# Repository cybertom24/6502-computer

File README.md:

# 6502-computer
My personal repo to build a breadboard version of a computer around the 6502 uProcessor. This project is inspired by the 6502 computer made by Ben Eater (https://eater.net/6502)

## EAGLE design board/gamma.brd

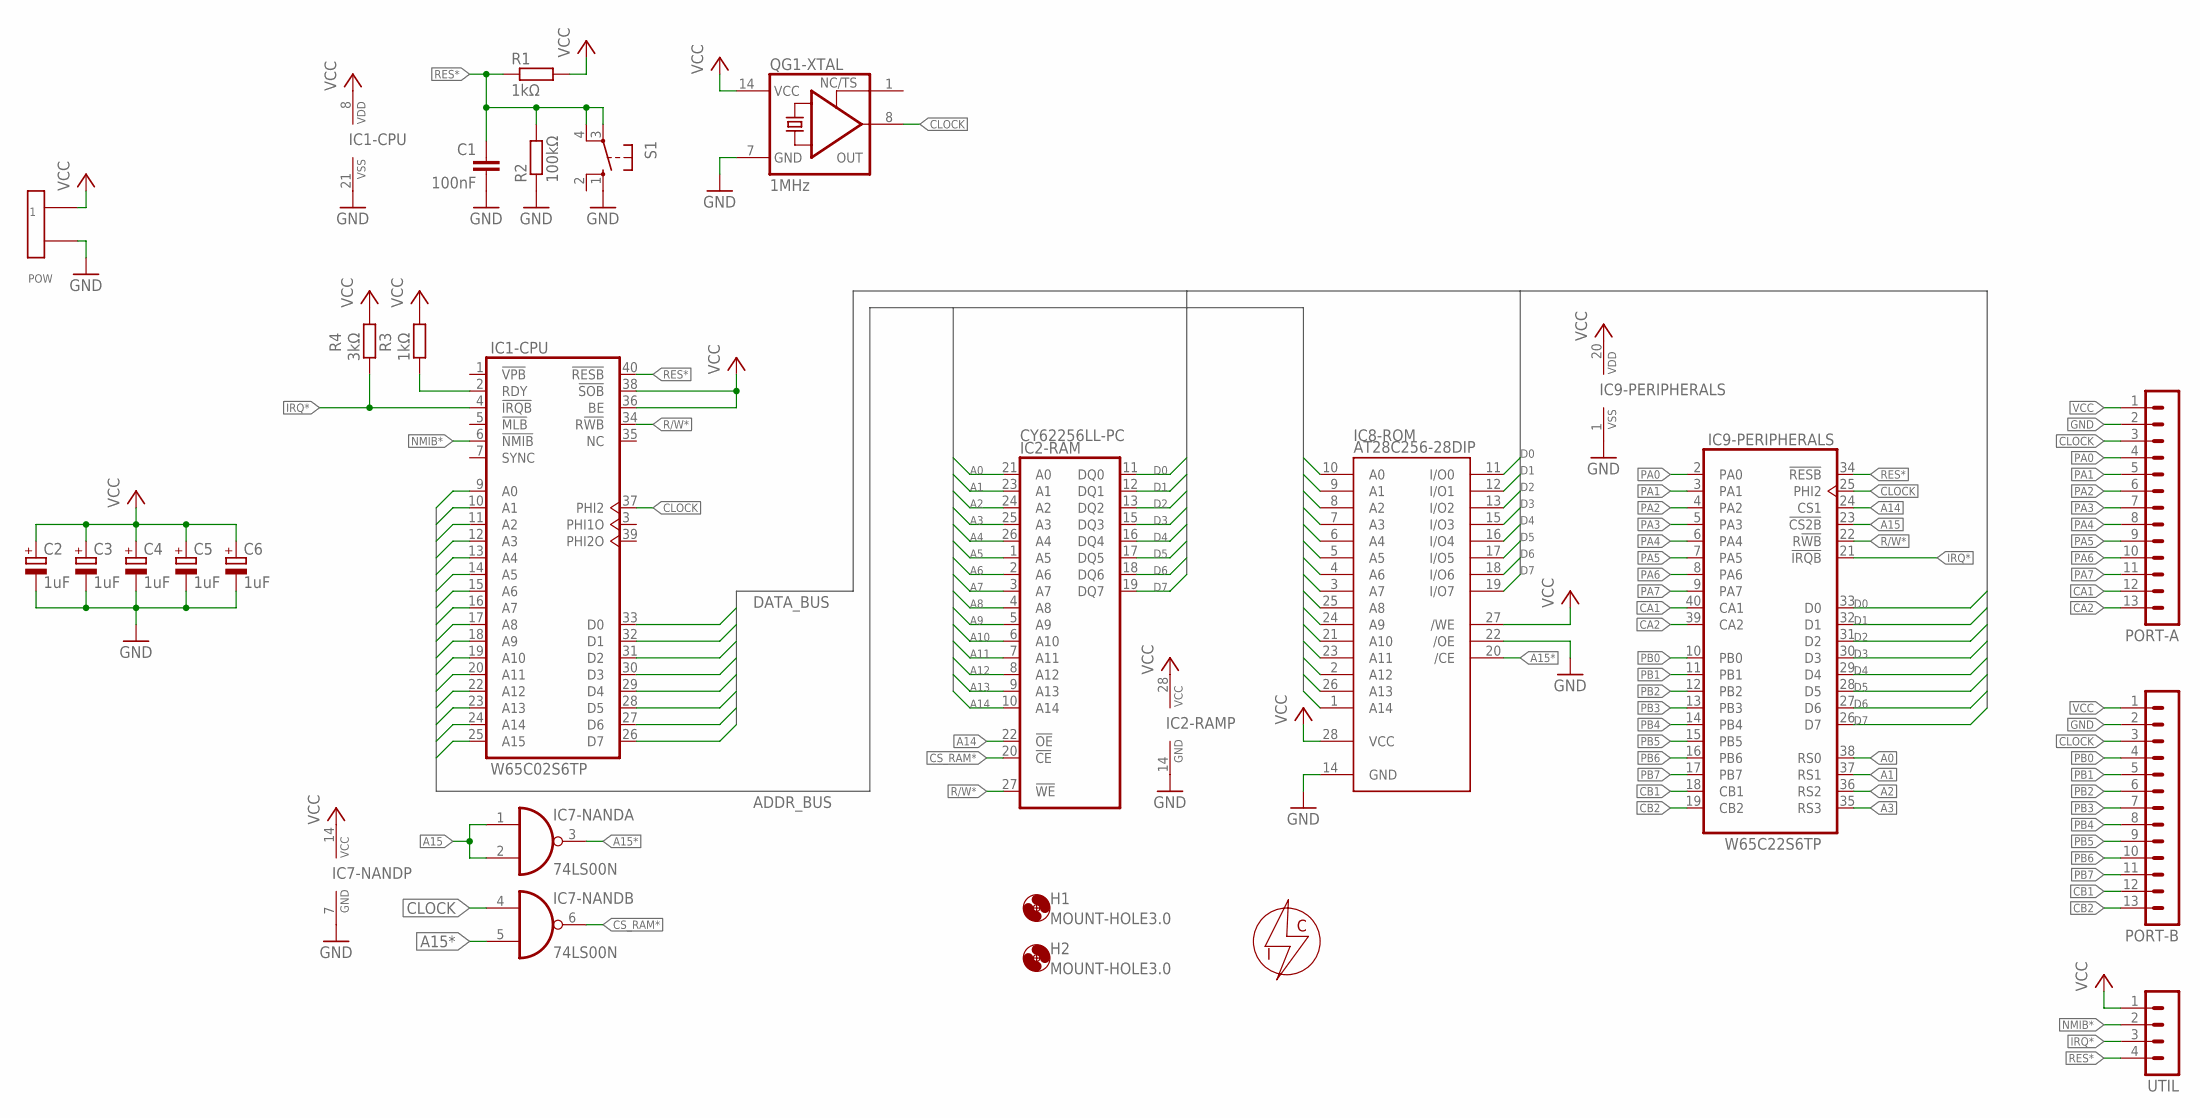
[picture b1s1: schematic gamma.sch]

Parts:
C1: 100nF; C050-025X075
C2, C3, C4, C5, C6: 1uF; E2-5
H1, H2: MOUNT-HOLE3.0; 3,0
IC1-CPU: W65C02S6TP; DIL40
IC2-RAM: CY62256LL-PC; DIL28-6
IC7-NAND: 74LS00N; DIL14
IC8-ROM: AT28C256-28DIP; DIL28-6
IC9-PERIPHERALS: W65C22S6TP; DIL40
PORT-A: MA13-1
PORT-B: MA13-1
POW: AK500; AK500-2
QG1-XTAL: 1MHz; DIL14S
R1, R3: 1kΩ; 0207/10
R2: 100kΩ; 0207/10
R4: 3kΩ; 0207/10
S1: 10-XX; B3F-10XX
U$1: LOGO-CYBERINDUSTRIES"; LOGO-SMALL
UTIL: MA04-1

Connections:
A0: IC1-CPU.9 (A0), IC2-RAM.21 (A0), IC8-ROM.10 (A0), IC9-PERIPHERALS.38 (RS0)
A1: IC1-CPU.10 (A1), IC2-RAM.23 (A1), IC8-ROM.9 (A1), IC9-PERIPHERALS.37 (RS1)
A2: IC1-CPU.11 (A2), IC2-RAM.24 (A2), IC8-ROM.8 (A2), IC9-PERIPHERALS.36 (RS2)
A3: IC1-CPU.12 (A3), IC2-RAM.25 (A3), IC8-ROM.7 (A3), IC9-PERIPHERALS.35 (RS3)
A4: IC1-CPU.13 (A4), IC2-RAM.26 (A4), IC8-ROM.6 (A4)
A5: IC1-CPU.14 (A5), IC2-RAM.1 (A5), IC8-ROM.5 (A5)
A6: IC1-CPU.15 (A6), IC2-RAM.2 (A6), IC8-ROM.4 (A6)
A7: IC1-CPU.16 (A7), IC2-RAM.3 (A7), IC8-ROM.3 (A7)
A8: IC1-CPU.17 (A8), IC2-RAM.4 (A8), IC8-ROM.25 (A8)
A9: IC1-CPU.18 (A9), IC2-RAM.5 (A9), IC8-ROM.24 (A9)
A10: IC1-CPU.19 (A10), IC2-RAM.6 (A10), IC8-ROM.21 (A10)
A11: IC1-CPU.20 (A11), IC2-RAM.7 (A11), IC8-ROM.23 (A11)
A12: IC1-CPU.22 (A12), IC2-RAM.8 (A12), IC8-ROM.2 (A12)
A13: IC1-CPU.23 (A13), IC2-RAM.9 (A13), IC8-ROM.26 (A13)
A14: IC1-CPU.24 (A14), IC2-RAM.10 (A14), IC2-RAM.22 (!OE), IC8-ROM.1 (A14), IC9-PERIPHERALS.24 (CS1)
A15: IC1-CPU.25 (A15), IC7-NAND.1 (I0), IC7-NAND.2 (I1), IC9-PERIPHERALS.23 (!CS2B)
A15*: IC7-NAND.3 (O), IC7-NAND.5 (I1), IC8-ROM.20 (/CE)
CA1: IC9-PERIPHERALS.40 (CA1), PORT-A.12
CA2: IC9-PERIPHERALS.39 (CA2), PORT-A.13
CB1: IC9-PERIPHERALS.18 (CB1), PORT-B.12
CB2: IC9-PERIPHERALS.19 (CB2), PORT-B.13
CLOCK: IC1-CPU.37 (PHI2), IC7-NAND.4 (I0), IC9-PERIPHERALS.25 (PHI2), PORT-A.3, PORT-B.3, QG1-XTAL.8 (OUT)
CS_RAM*: IC2-RAM.20 (!CE), IC7-NAND.6 (O)
D0: IC1-CPU.33 (D0), IC2-RAM.11 (DQ0), IC8-ROM.11 (I/O0), IC9-PERIPHERALS.33 (D0)
D1: IC1-CPU.32 (D1), IC2-RAM.12 (DQ1), IC8-ROM.12 (I/O1), IC9-PERIPHERALS.32 (D1)
D2: IC1-CPU.31 (D2), IC2-RAM.13 (DQ2), IC8-ROM.13 (I/O2), IC9-PERIPHERALS.31 (D2)
D3: IC1-CPU.30 (D3), IC2-RAM.15 (DQ3), IC8-ROM.15 (I/O3), IC9-PERIPHERALS.30 (D3)
D4: IC1-CPU.29 (D4), IC2-RAM.16 (DQ4), IC8-ROM.16 (I/O4), IC9-PERIPHERALS.29 (D4)
D5: IC1-CPU.28 (D5), IC2-RAM.17 (DQ5), IC8-ROM.17 (I/O5), IC9-PERIPHERALS.28 (D5)
D6: IC1-CPU.27 (D6), IC2-RAM.18 (DQ6), IC8-ROM.18 (I/O6), IC9-PERIPHERALS.27 (D6)
D7: IC1-CPU.26 (D7), IC2-RAM.19 (DQ7), IC8-ROM.19 (I/O7), IC9-PERIPHERALS.26 (D7)
GND: C1.2, C2.-, C3.-, C4.-, C5.-, C6.-, IC1-CPU.21 (VSS), IC2-RAM.14 (GND), IC7-NAND.7 (GND), IC8-ROM.14 (GND), IC8-ROM.22 (/OE), IC9-PERIPHERALS.1 (VSS), PORT-A.2, PORT-B.2, POW.P$2, QG1-XTAL.7 (GND), R2.1, S1.1 (S)
IRQ*: IC1-CPU.4 (!IRQB), IC9-PERIPHERALS.21 (!IRQB), R4.2, UTIL.3
unnamed: IC1-CPU.2 (RDY), R3.2
NMIB*: IC1-CPU.6 (!NMIB), UTIL.2
PA0: IC9-PERIPHERALS.2 (PA0), PORT-A.4
PA1: IC9-PERIPHERALS.3 (PA1), PORT-A.5
PA2: IC9-PERIPHERALS.4 (PA2), PORT-A.6
PA3: IC9-PERIPHERALS.5 (PA3), PORT-A.7
PA4: IC9-PERIPHERALS.6 (PA4), PORT-A.8
PA5: IC9-PERIPHERALS.7 (PA5), PORT-A.9
PA6: IC9-PERIPHERALS.8 (PA6), PORT-A.10
PA7: IC9-PERIPHERALS.9 (PA7), PORT-A.11
PB0: IC9-PERIPHERALS.10 (PB0), PORT-B.4
PB1: IC9-PERIPHERALS.11 (PB1), PORT-B.5
PB2: IC9-PERIPHERALS.12 (PB2), PORT-B.6
PB3: IC9-PERIPHERALS.13 (PB3), PORT-B.7
PB4: IC9-PERIPHERALS.14 (PB4), PORT-B.8
PB5: IC9-PERIPHERALS.15 (PB5), PORT-B.9
PB6: IC9-PERIPHERALS.16 (PB6), PORT-B.10
PB7: IC9-PERIPHERALS.17 (PB7), PORT-B.11
R/W*: IC1-CPU.34 (R!WB), IC2-RAM.27 (!WE), IC9-PERIPHERALS.22 (R!WB)
RES*: C1.1, IC1-CPU.40 (!RESB), IC9-PERIPHERALS.34 (!RESB), R1.1, R2.2, S1.3, S1.4 (P1), UTIL.4
VCC: C2.+, C3.+, C4.+, C5.+, C6.+, IC1-CPU.8 (VDD), IC1-CPU.36 (BE), IC1-CPU.38 (!SOB), IC2-RAM.28 (VCC), IC7-NAND.14 (VCC), IC8-ROM.27 (/WE), IC8-ROM.28 (VCC), IC9-PERIPHERALS.20 (VDD), PORT-A.1, PORT-B.1, POW.P$1, QG1-XTAL.14 (VCC), R1.2, R3.1, R4.1, UTIL.1

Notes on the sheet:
DATA_BUS
ADDR_BUS

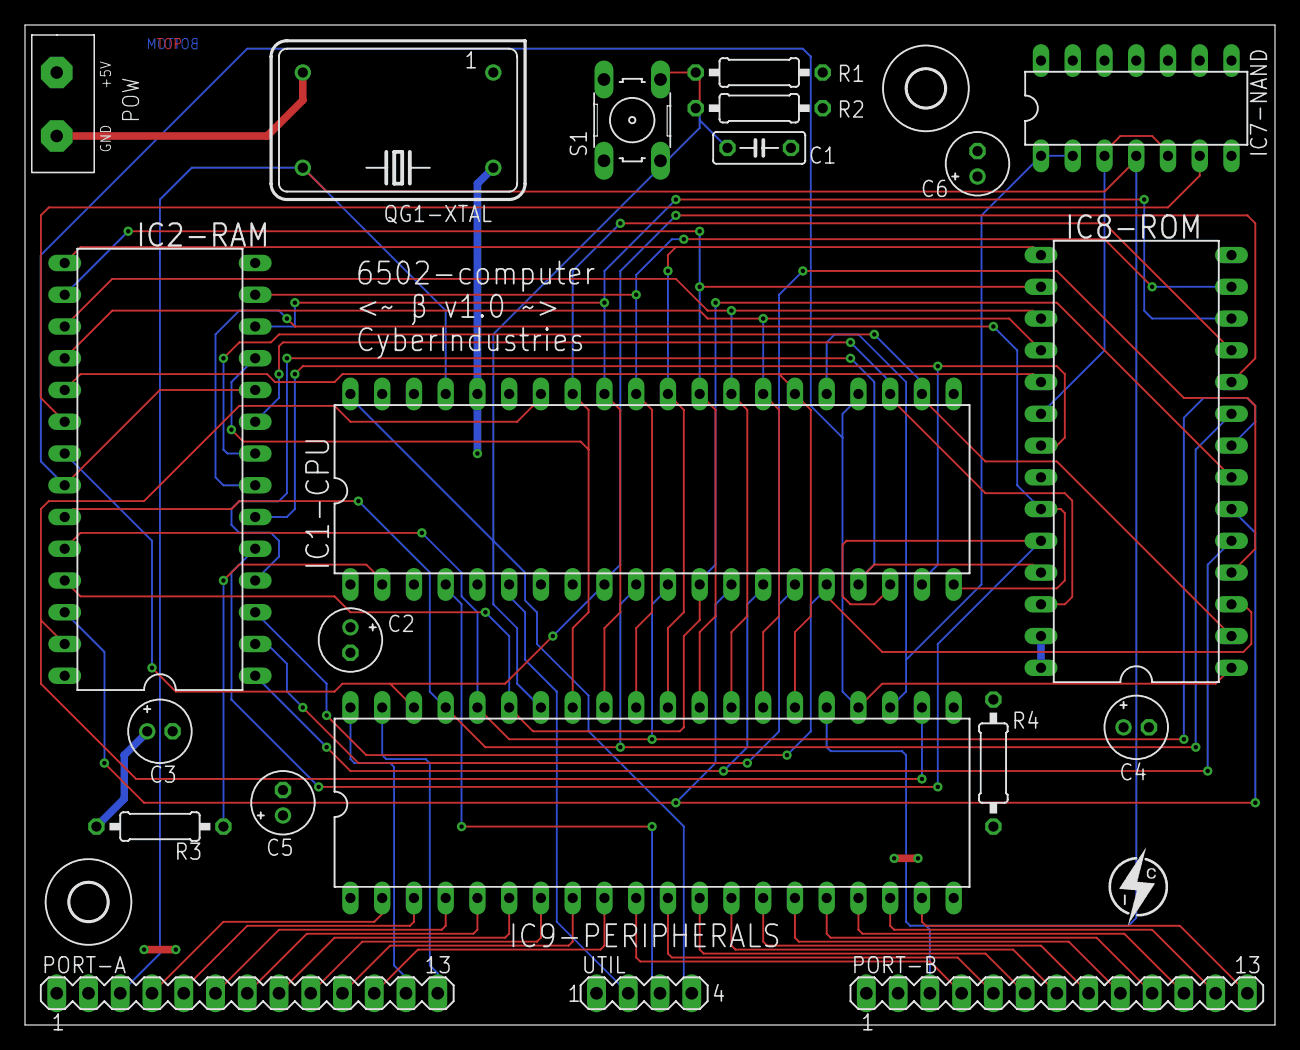
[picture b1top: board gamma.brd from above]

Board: 2 copper layers, 100.0 x 80.0 mm, 24 parts (0 on the bottom side), 54 nets.

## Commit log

2022-07-15 uploading old files
2022-07-15 added schematic main board
2022-07-15 imageù
2022-07-15 updated schematic
2022-07-20 downloaded emu6502, created ROMImage script, modified board
2022-07-22 modified board
2022-07-24 added 555 circuit
2022-07-28 created display board
2022-07-29 created ROMImage script in python and added LCD display to the schematic
2022-07-29 created ROMImage in python
2022-08-02 varius things
2022-08-23 added lcd
2022-08-24 porco dio
2022-09-09 ciao
2022-09-21 made new programs and extended lcd.65s
2023-03-30 fatto pcb
2023-03-30 completato pcb
2023-04-05 sistemato pcb
2023-07-19 Modificate schede, creati file ASM
2023-09-11 using vs code instead of 6502.exe, using board with 1 MHz clock
2024-02-10 tanta ma tanta roba
2024-03-26 working kbrd reader on arduino
2024-10-10 roba
